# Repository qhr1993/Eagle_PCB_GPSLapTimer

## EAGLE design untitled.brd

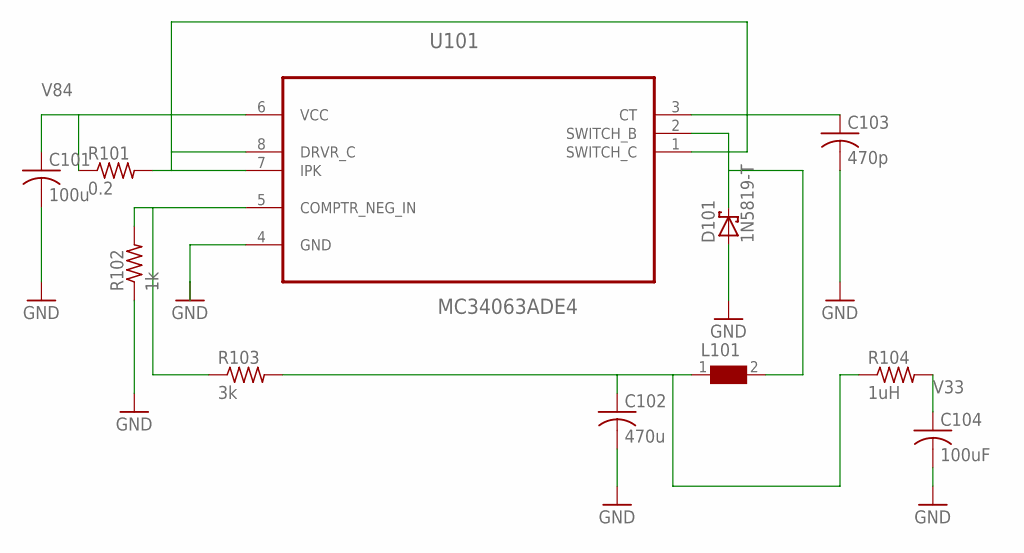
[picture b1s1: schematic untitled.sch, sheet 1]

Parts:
C101: 100u; C0805
C102: 470u; C0805
C103: 470p; C0805
C104: 100uF; C0805
D101: 1N5819-T; DO41-7.6
L101: WE-PD-7447714101_1030/1050; WE-PD_1030/1050
R101: 0.2; R0805
R102: 1k; R0805
R103: 3k; R0805
R104: 1uH; R0805
U101: MC34063ADE4; SOIC127P600X175-8N

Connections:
GND: C101.2, C102.2, C103.2, C104.2, D101.A, R102.1, U101.4 (GND); also elsewhere on the board
unnamed: C103.1, U101.3 (CT)
unnamed: R102.2, R103.1, U101.5 (COMPTR_NEG_IN)
unnamed: C102.1, L101.1, R103.2, R104.1
unnamed: R101.2, U101.1 (SWITCH_C), U101.7 (IPK), U101.8 (DRVR_C)
unnamed: D101.C, L101.2, U101.2 (SWITCH_B)
V33: C104.1, R104.2; also elsewhere on the board
V84: C101.1, R101.1, U101.6 (VCC); also elsewhere on the board

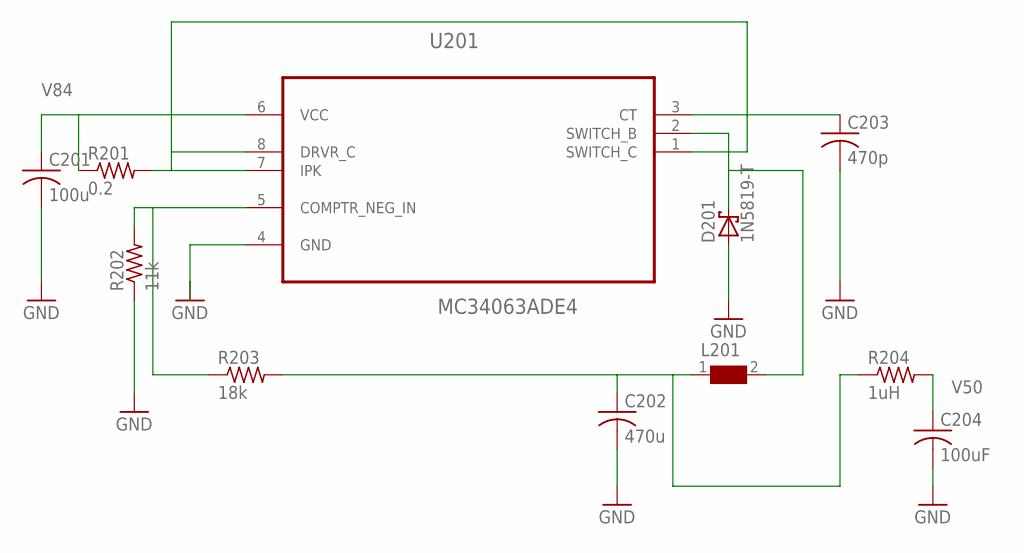
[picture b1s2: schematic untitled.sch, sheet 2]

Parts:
C201: 100u; C0805
C202: 470u; C0805
C203: 470p; C0805
C204: 100uF; C0805
D201: 1N5819-T; DO41-7.6
L201: WE-PD-7447714101_1030/1050; WE-PD_1030/1050
R201: 0.2; R0805
R202: 11k; R0805
R203: 18k; R0805
R204: 1uH; R0805
U201: MC34063ADE4; SOIC127P600X175-8N

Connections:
GND: C201.2, C202.2, C203.2, C204.2, D201.A, R202.1, U201.4 (GND); also elsewhere on the board
unnamed: C203.1, U201.3 (CT)
unnamed: R202.2, R203.1, U201.5 (COMPTR_NEG_IN)
unnamed: C202.1, L201.1, R203.2, R204.1
unnamed: R201.2, U201.1 (SWITCH_C), U201.7 (IPK), U201.8 (DRVR_C)
unnamed: D201.C, L201.2, U201.2 (SWITCH_B)
V50: C204.1, R204.2; also elsewhere on the board
V84: C201.1, R201.1, U201.6 (VCC); also elsewhere on the board

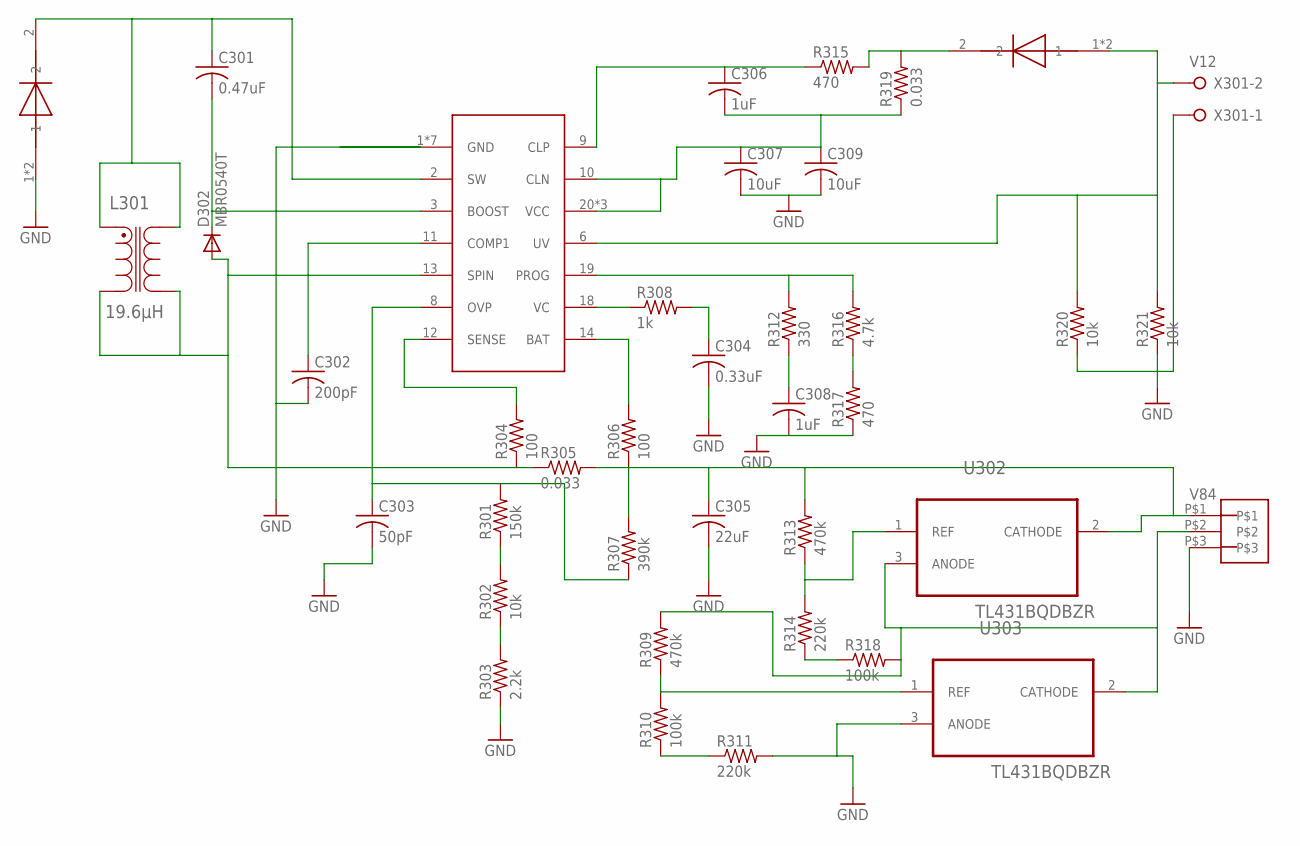
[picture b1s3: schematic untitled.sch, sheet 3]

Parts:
C301: 0.47uF; C0805
C302: 200pF; C0805
C303: 50pF; C0805
C304: 0.33uF; C0805
C305: 22uF; C0805
C306, C308: 1uF; C0805
C307, C309: 10uF; C0805
D301, D303: MBRD340; DPACK
D302: MBR0540T; SOD-123_MINI-SMA
J301: 3_PIN_JST-XH
L301: 19.6µH; INDM115115X635N
R301: 150k; R0805
R302, R320, R321: 10k; R0805
R303: 2.2k; R0805
R304, R306: 100; R0805
R305, R319: 0.033; R0805
R307: 390k; R0805
R308: 1k; R0805
R309, R313: 470k; R0805
R310, R318: 100k; R0805
R311, R314: 220k; R0805
R312: 330; R0805
R315, R317: 470; R0805
R316: 4.7k; R0805
U301: LT1511; SO24W
U302, U303: TL431BQDBZR; SOT95P237X112-3N
X301: W237-02P; W237-132

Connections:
GND: C302.2, C303.2, C304.2, C305.2, C307.2, C308.2, C309.2, D301.1, D301.3 (1), J301.P$3, R303.1, R311.2, R317.1, R320.1, R321.1, U301.1 (GND), U301.4 (GND), U301.5 (GND), U301.7 (GND), U301.16 (GND), U301.23 (GND), U301.24 (GND), U303.3 (ANODE), X301.1; also elsewhere on the board
unnamed: C301.1, D301.2, L301.1, L301.4, U301.2 (SW)
unnamed: D302.A, L301.2, L301.3, R304.1, R305.1, U301.13 (SPIN)
unnamed: C301.2, D302.C, U301.3 (BOOST)
unnamed: C302.1, U301.11 (COMP1)
unnamed: R304.2, U301.12 (SENSE)
unnamed: R306.2, U301.14 (BAT)
unnamed: R308.1, U301.18 (VC)
unnamed: C304.1, R308.2
unnamed: R312.2, R316.2, U301.19 (PROG)
unnamed: C308.1, R312.1
unnamed: C306.2, C307.1, C309.1, R319.1, U301.10 (CLN), U301.20 (VCC), U301.21 (VCC), U301.22 (VCC)
unnamed: C306.1, R315.1, U301.9 (CLP)
unnamed: D303.2, R315.2, R319.2
unnamed: R301.1, R302.2
unnamed: R302.1, R303.2
unnamed: R316.1, R317.2
unnamed: C303.1, R301.2, R307.1, U301.8 (OVP)
unnamed: R314.1, R318.1
unnamed: R313.1, R314.2, U302.1 (REF)
unnamed: R309.1, R310.2, U303.1 (REF)
unnamed: R310.1, R311.1
unnamed: J301.P$2, R309.2, R318.2, U302.3 (ANODE), U303.2 (CATHODE)
V12: D303.1, D303.3 (1), R320.2, R321.2, U301.6 (UV), X301.2
V84: C305.1, J301.P$1, R305.2, R306.1, R307.2, R313.2, U302.2 (CATHODE); also elsewhere on the board

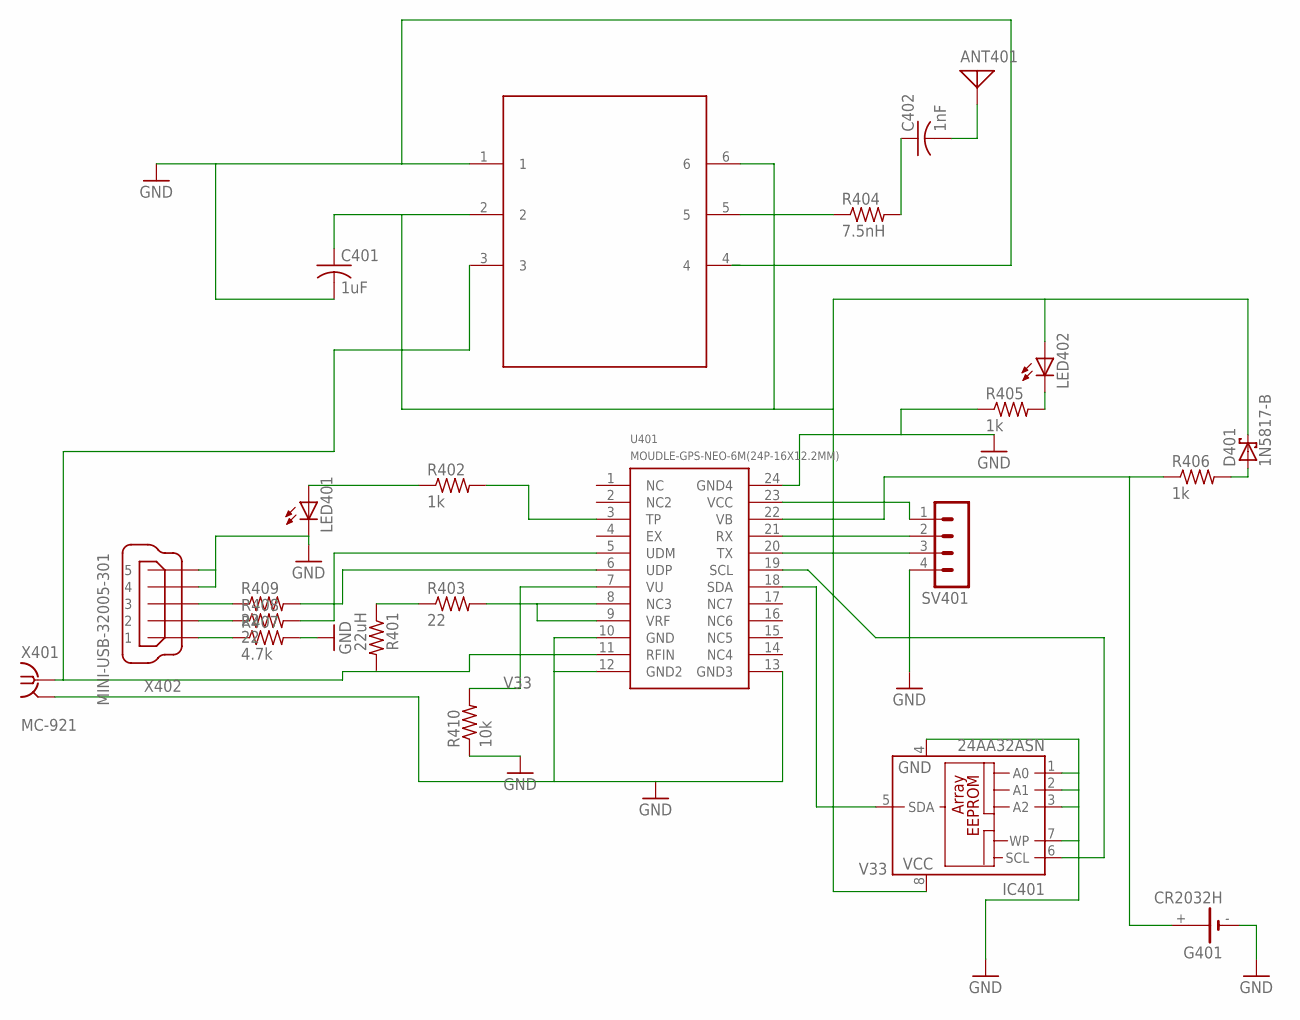
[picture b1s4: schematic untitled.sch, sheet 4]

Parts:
ANT401: ANTENNA; PAD-01
C401: 1uF; C0603
C402: 1nF; C0603
D401: 1N5817-B; DO41-7.6
G401: CR2032H
IC401: 24AA32ASN; SO-08
LED401, LED402: LEDCHIP-LED0805; CHIP-LED0805
R401: 22uH; R0603
R402, R405, R406: 1k; R0805
R403, R408, R409: 22; R0603
R404: 7.5nH; R0603
R407: 4.7k; R0603
R410: 10k; R0603
SV401: MA04-1
U401: MOUDLE-GPS-NEO-6M(24P-16X12.2MM); GPS24P-SMD-1.1-16X12.2MM
U402: INF-TSLP-6-2_V_1; INF-TSLP-6-2_V_1PRIMARY
X401: MC-921
X402: MINI-USB-32005-301; 32005-301

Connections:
GND: C401.2, G401.-, IC401.1 (A0), IC401.2 (A1), IC401.3 (A2), IC401.4 (GND), IC401.7 (WP), LED401.C, R405.1, R407.2, R410.1, SV401.4, U401.10 (GND), U401.12 (GND2), U401.13 (GND3), U401.24 (GND4), U402.1, X401.2@1 (GND), X401.2@2 (GND), X402.4, X402.5; also elsewhere on the board
unnamed: LED401.A, R402.1
unnamed: SV401.3, U401.20 (TX)
unnamed: SV401.2, U401.21 (RX)
unnamed: IC401.6 (SCL), U401.19 (SCL)
unnamed: IC401.5 (SDA), U401.18 (SDA)
unnamed: R402.2, U401.3 (TP)
unnamed: R403.2, U401.8 (NC3), U401.9 (VRF)
unnamed: G401.+, R406.1, U401.22 (VB)
unnamed: D401.A, R406.2
unnamed: LED402.C, R405.2
unnamed: R401.1, R403.1
unnamed: R408.2, U401.5 (UDM)
unnamed: R409.2, U401.6 (UDP)
unnamed: ANT401.1, C402.2
unnamed: R401.2, U401.11 (RFIN), U402.3, X401.1
unnamed: R404.1, U402.5
unnamed: C402.1, R404.2
unnamed: R407.1, X402.1
unnamed: R409.1, X402.3
unnamed: R408.1, X402.2
V33: C401.1, D401.C, IC401.8 (VCC), LED402.A, R410.2, SV401.1, U401.7 (VU), U401.23 (VCC), U402.2, U402.6; also elsewhere on the board

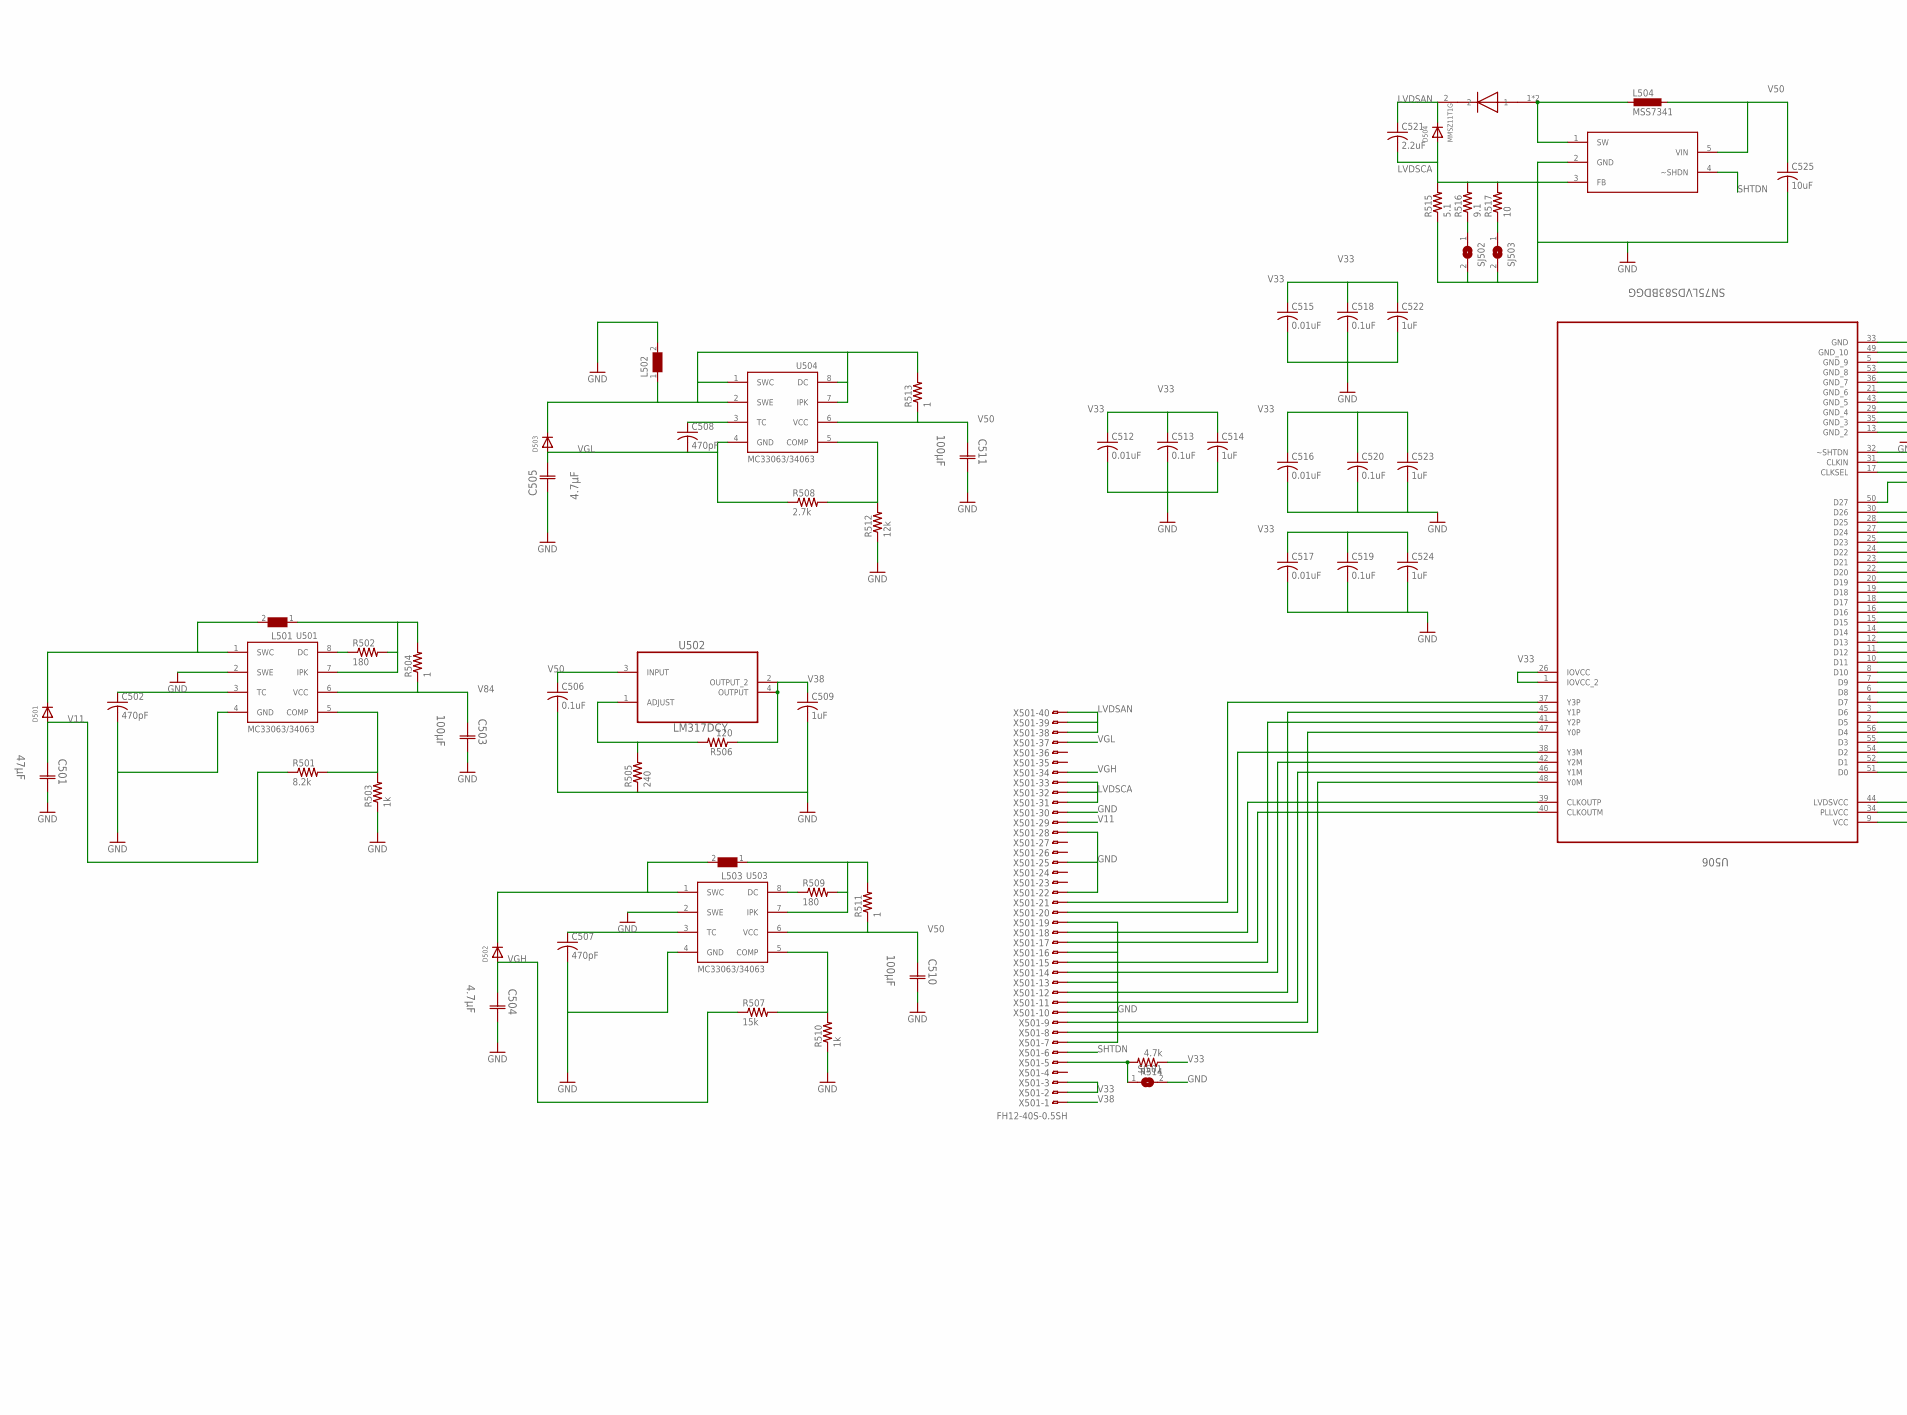
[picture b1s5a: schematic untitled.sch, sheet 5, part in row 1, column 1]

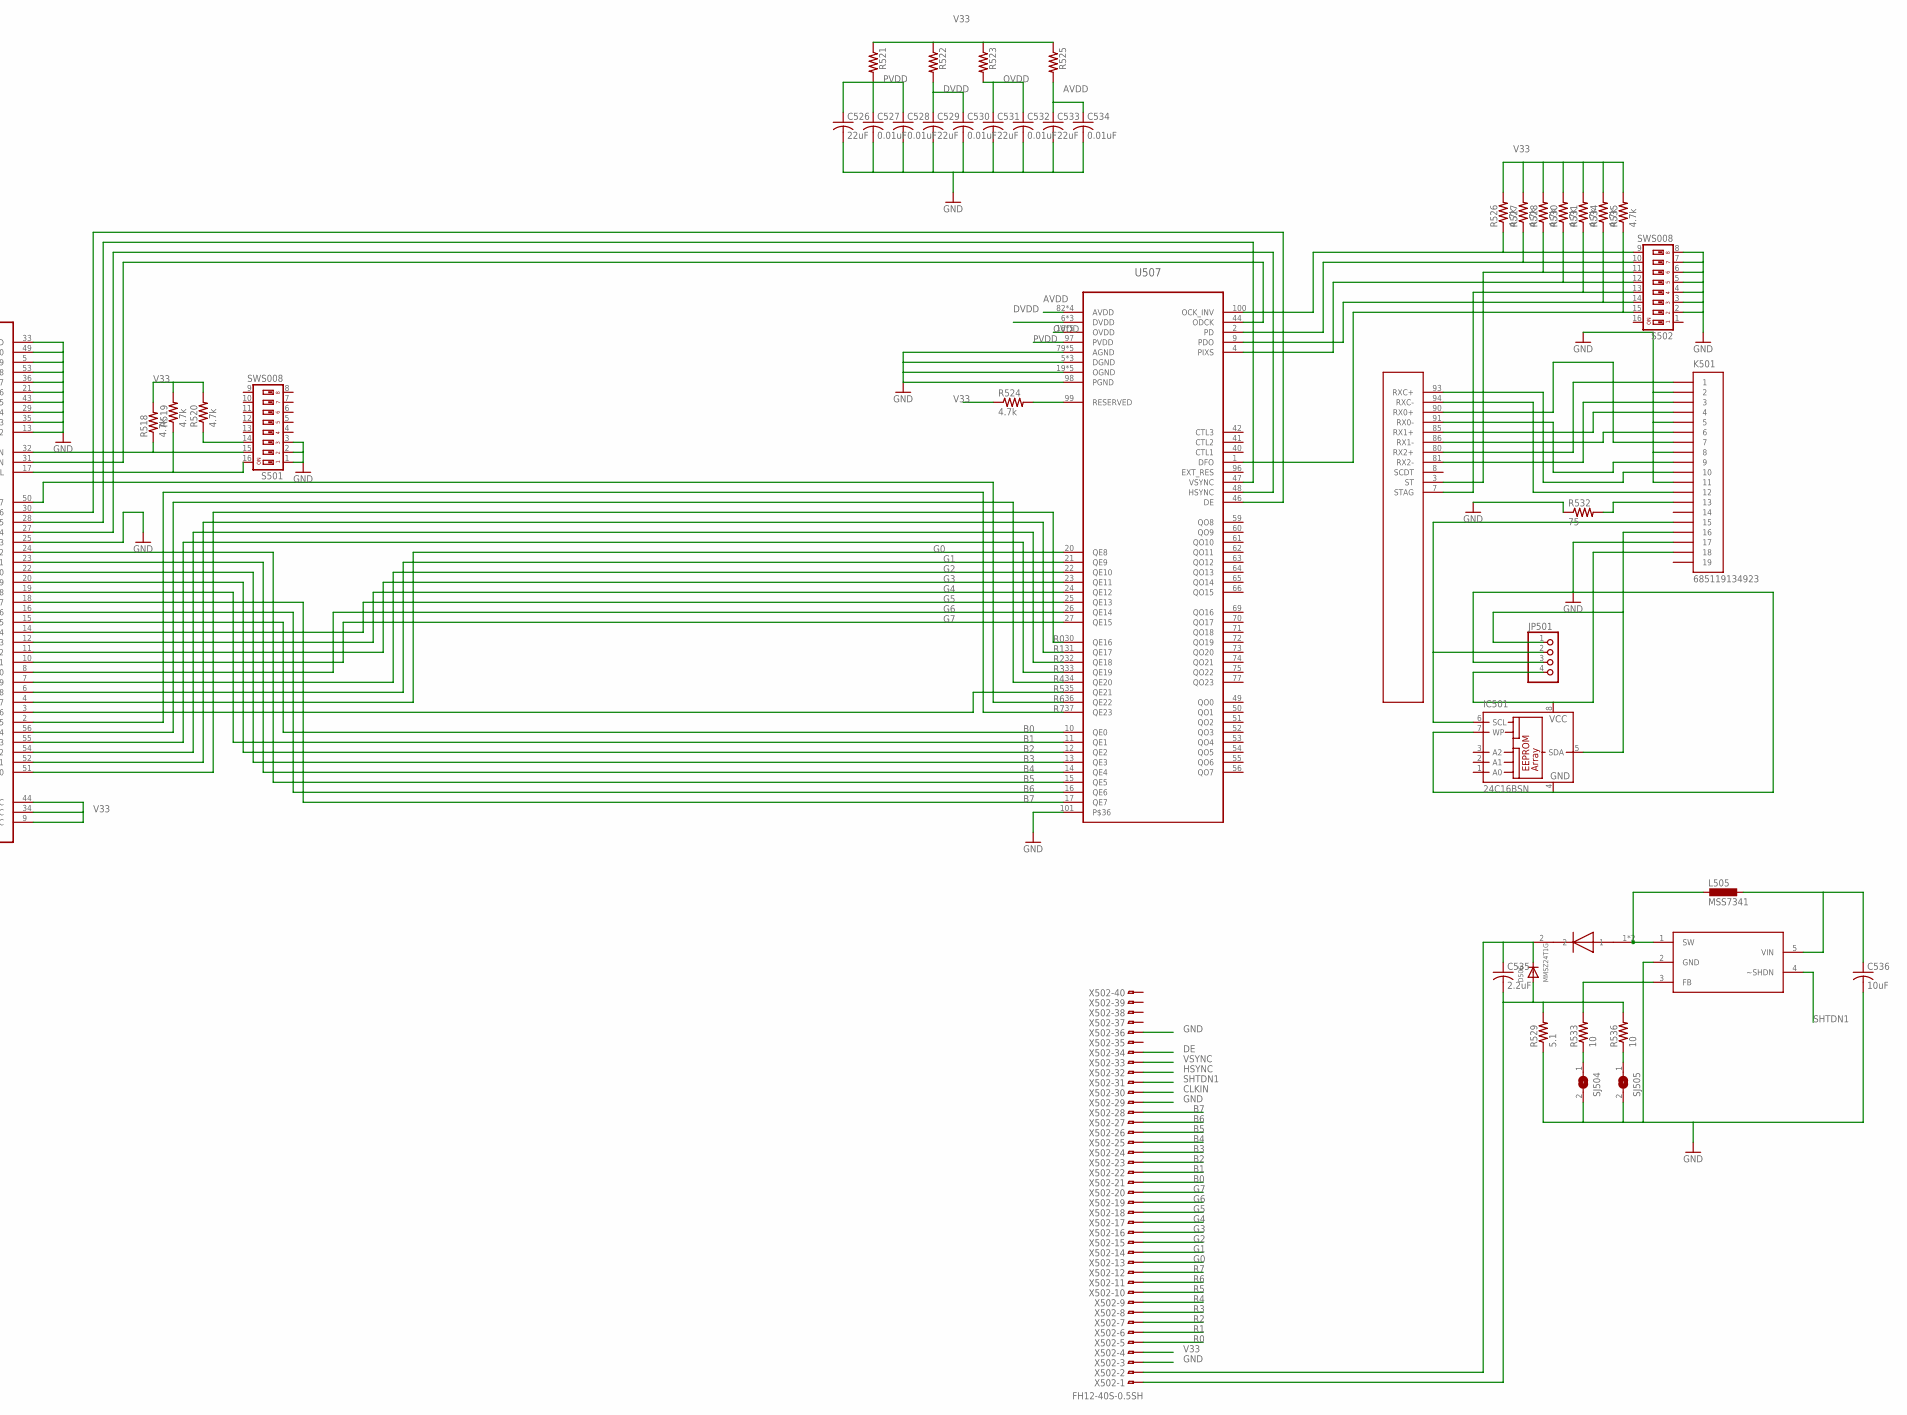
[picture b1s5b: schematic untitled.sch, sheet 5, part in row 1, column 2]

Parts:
C501: 47µF; CAPCP6032X280N
C502, C507, C508: 470pF; C0603
C503, C510, C511: 100µF; CAPCP6032X280N
C504, C505: 4.7µF; CAPCP6032X280N
C506, C513, C518, C519, C520: 0.1uF; C0603
C509, C514, C522, C523, C524: 1uF; C0603
C512, C515, C516, C517, C527, C528, C530, C532, C534: 0.01uF; C0603
C521, C535: 2.2uF; C0805
C525, C536: 10uF; C0805
C526, C529, C531, C533: 22uF; C0603
D501, D502, D503: DIODESOD-123; SOD-123
D504: MMSZ11T1G; SOD-123
D505, D507: MBRD340; DPACK
D506: MMSZ24T1G; SOD-123
IC501: 24C16BSN; SO-08
JP501: PINHD-1X4; 1X04
K501: 685119134923
L501, L502, L503: WE-PD-7447714101_1030/1050; WE-PD_1030/1050
L504, L505: MSS7341
R501: 8.2k; R0603
R502, R509: 180; R0603
R503, R510: 1k; R0603
R504, R511, R513: 1; R0603
R505: 240; R0603
R506: 120; R0603
R507: 15k; R0603
R508: 2.7k; R0603
R512: 12k; R0603
R514, R518, R519, R520, R524, R526, R527, R528, R530, R531, R534, R535: 4.7k; R0603
R515, R529: 5.1; R0603
R516: 9.1; R0603
R517, R533, R536: 10; R0603
R521, R522, R523, R525: R-US_R0805; R0805
R532: 75; R0603
S501, S502: SWS008; SMS-008
SJ501, SJ502, SJ503, SJ504, SJ505: SJ
U501, U503, U504: MC33063/MC34063D; SO08
U502: LM317DCY; SOT230P700X180-4N
U505, U508: FAN5333BSX; SOT23-5L
U506: SN75LVDS83BDGG; SOP50P810X120-56N
U507: TPF401; QFP50P1600X1600X120-101N
X501, X502: FH12-40S-0.5SH

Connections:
AVDD: C533.1, C534.1, R525.2, U507.82 (AVDD), U507.84 (AVDD), U507.88 (AVDD), U507.95 (AVDD)
B0: U506.15 (D15), U507.10 (QE0), X502.21
B1: U506.19 (D18), U507.11 (QE1), X502.22
B2: U506.20 (D19), U507.12 (QE2), X502.23
B3: U506.22 (D20), U507.13 (QE3), X502.24
B4: U506.23 (D21), U507.14 (QE4), X502.25
B5: U506.24 (D22), U507.15 (QE5), X502.26
B6: U506.16 (D16), U507.16 (QE6), X502.27
B7: U506.18 (D17), U507.17 (QE7), X502.28
CLKIN: U506.31 (CLKIN), U507.44 (ODCK), X502.30
DE: U506.30 (D26), U507.46 (DE), X502.34
DVDD: C529.1, C530.1, R522.2, U507.6 (DVDD), U507.38 (DVDD), U507.67 (DVDD)
G0: U506.4 (D7), U507.20 (QE8), X502.13
G1: U506.6 (D8), U507.21 (QE9), X502.14
G2: U506.7 (D9), U507.22 (QE10), X502.15
G3: U506.11 (D12), U507.23 (QE11), X502.16
G4: U506.12 (D13), U507.24 (QE12), X502.17
G5: U506.14 (D14), U507.25 (QE13), X502.18
G6: U506.8 (D10), U507.26 (QE14), X502.19
G7: U506.10 (D11), U507.27 (QE15), X502.20
GND: C501.2 (C2), C502.2, C503.2 (C2), C504.2 (C2), C505.1 (C1), C506.2, C507.2, C509.2, C510.2 (C2), C511.2 (C2), C512.2, C513.2, C514.2, C515.2, C516.2, C517.2, C518.2, C519.2, C520.2, C522.2, C523.2, C524.2, C525.2, C526.2, C527.2, C528.2, C529.2, C530.2, C531.2, C532.2, C533.2, C534.2, C536.2, IC501.4 (GND), IC501.7 (WP), JP501.3, K501.2, K501.5, K501.8, K501.11, K501.17, L502.2, R503.1, R505.1, R510.1, R512.1, R515.1, R529.1, R532.1, S501.1, S501.2, S501.3, S502.2, S502.3, S502.4, S502.5, S502.6, S502.7, S502.8, SJ501.2, SJ502.2, SJ503.2, SJ504.2, SJ505.2, U501.2 (SWE), U501.4 (GND), U503.2 (SWE), U503.4 (GND), U505.2 (GND), U506.5 (GND_9), U506.13 (GND_2), U506.21 (GND_6), U506.25 (D23), U506.29 (GND_4), U506.33 (GND), U506.35 (GND_3), U506.36 (GND_7), U506.43 (GND_5), U506.49 (GND_10), U506.53 (GND_8), U507.5 (DGND), U507.19 (OGND), U507.28 (OGND), U507.39 (DGND), U507.45 (OGND), U507.58 (OGND), U507.68 (DGND), U507.76 (OGND), U507.79 (AGND), U507.83 (AGND), U507.87 (AGND), U507.89 (AGND), U507.92 (AGND), U507.98 (PGND), U507.101, U508.2 (GND), X501.7, X501.10, X501.13, X501.16, X501.19, X501.22, X501.25, X501.28, X501.30, X502.3, X502.29, X502.36; also elsewhere on the board
HSYNC: U506.27 (D24), U507.48 (HSYNC), X502.32
LVDSAN: C521.1, D504.C, D505.2, X501.38, X501.39, X501.40
LVDSCA: C521.2, D504.A, R515.2, R516.2, R517.2, U505.3 (FB), X501.31, X501.32, X501.33
unnamed: R524.2, U507.99 (RESERVED)
unnamed: R526.1, S502.9, U507.100 (OCK_INV)
unnamed: R527.1, S502.10, U507.2 (PD)
unnamed: R528.1, S502.11, U507.3 (ST)
unnamed: R530.1, S502.12, U507.4 (PIXS)
unnamed: R531.1, S502.13, U507.7 (STAG)
unnamed: R534.1, S502.14, U507.9 (PDO)
unnamed: R535.1, S502.15, U507.1 (DFO)
unnamed: K501.1, U507.80 (RX2+)
unnamed: K501.3, U507.81 (RX2-)
unnamed: K501.4, U507.85 (RX1+)
unnamed: K501.6, U507.86 (RX1-)
unnamed: K501.7, U507.90 (RX0+)
unnamed: K501.9, U507.91 (RX0-)
unnamed: K501.10, U507.93 (RXC+)
unnamed: K501.12, U507.94 (RXC-)
unnamed: IC501.8 (VCC), JP501.4, K501.18
unnamed: IC501.6 (SCL), JP501.2, K501.15
unnamed: IC501.5 (SDA), JP501.1, K501.16
unnamed: K501.13, R532.2
unnamed: D505.1, D505.3 (1), L504.1, U505.1 (SW)
unnamed: R516.1, SJ502.1
unnamed: R517.1, SJ503.1
unnamed: D507.1, D507.3 (1), L505.1, U508.1 (SW)
unnamed: C535.1, D506.C, D507.2, X502.2
unnamed: C535.2, D506.A, R529.2, R533.2, R536.2, U508.3 (FB), X502.1
unnamed: R536.1, SJ505.1
unnamed: R533.1, SJ504.1
unnamed: C508.1, U504.3 (TC)
unnamed: D503.C, L502.1, R513.2, U504.1 (SWC), U504.2 (SWE), U504.7 (IPK), U504.8 (DC)
unnamed: R508.2, R512.2, U504.5 (COMP)
unnamed: U506.37 (Y3P), X501.21
unnamed: U506.38 (Y3M), X501.20
unnamed: U506.39 (CLKOUTP), X501.18
unnamed: U506.40 (CLKOUTM), X501.17
unnamed: U506.41 (Y2P), X501.15
unnamed: U506.42 (Y2M), X501.14
unnamed: U506.45 (Y1P), X501.12
unnamed: U506.46 (Y1M), X501.11
unnamed: U506.47 (Y0P), X501.9
unnamed: U506.48 (Y0M), X501.8
unnamed: R505.2, R506.2, U502.1 (ADJUST)
unnamed: R514.2, SJ501.1, X501.5
unnamed: R519.1, S501.16, U506.17 (CLKSEL)
unnamed: C507.1, U503.3 (TC)
unnamed: D502.C, L503.2, U503.1 (SWC)
unnamed: R507.2, R510.2, U503.5 (COMP)
unnamed: L503.1, R509.2, R511.2, U503.7 (IPK)
unnamed: R509.1, U503.8 (DC)
unnamed: C502.1, U501.3 (TC)
unnamed: D501.C, L501.2, U501.1 (SWC)
unnamed: R501.2, R503.2, U501.5 (COMP)
unnamed: L501.1, R502.2, R504.2, U501.7 (IPK)
unnamed: R502.1, U501.8 (DC)
OVDD: C531.1, C532.1, R523.2, U507.18 (OVDD), U507.29 (OVDD), U507.43 (OVDD), U507.57 (OVDD), U507.78 (OVDD)
PVDD: C526.1, C527.1, C528.1, R521.2, U507.97 (PVDD)
R0: U506.51 (D0), U507.30 (QE16), X502.5
R1: U506.52 (D1), U507.31 (QE17), X502.6
R2: U506.54 (D2), U507.32 (QE18), X502.7
R3: U506.55 (D3), U507.33 (QE19), X502.8
R4: U506.56 (D4), U507.34 (QE20), X502.9
R5: U506.3 (D6), U507.35 (QE21), X502.10
R6: U506.50 (D27), U507.36 (QE22), X502.11
R7: U506.2 (D5), U507.37 (QE23), X502.12
SHTDN: R518.1, S501.15, U505.4 (~SHDN), U506.32 (~SHTDN), X501.6
SHTDN1: R520.1, S501.14, U508.4 (~SHDN), X502.31
V11: C501.1 (C1), D501.A, R501.1, X501.29
V33: C512.1, C513.1, C514.1, C515.1, C516.1, C517.1, C518.1, C519.1, C520.1, C522.1, C523.1, C524.1, R514.1, R518.2, R519.2, R520.2, R521.1, R522.1, R523.1, R524.1, R525.1, R526.2, R527.2, R528.2, R530.2, R531.2, R534.2, R535.2, U506.1 (IOVCC_2), U506.9 (VCC), U506.26 (IOVCC), U506.34 (PLLVCC), U506.44 (LVDSVCC), X501.2, X501.3, X502.4; also elsewhere on the board
V38: C509.1, R506.1, U502.2 (OUTPUT_2), U502.4 (OUTPUT), X501.1
V50: C506.1, C510.1 (C1), C511.1 (C1), C525.1, C536.1, L504.2, L505.2, R511.1, R513.1, U502.3 (INPUT), U503.6 (VCC), U504.6 (VCC), U505.5 (VIN), U508.5 (VIN); also elsewhere on the board
V84: C503.1 (C1), R504.1, U501.6 (VCC); also elsewhere on the board
VGH: C504.1 (C1), D502.A, R507.1, X501.34
VGL: C505.2 (C2), C508.2, D503.A, R508.1, U504.4 (GND), X501.37
VSYNC: U506.28 (D25), U507.47 (VSYNC), X502.33

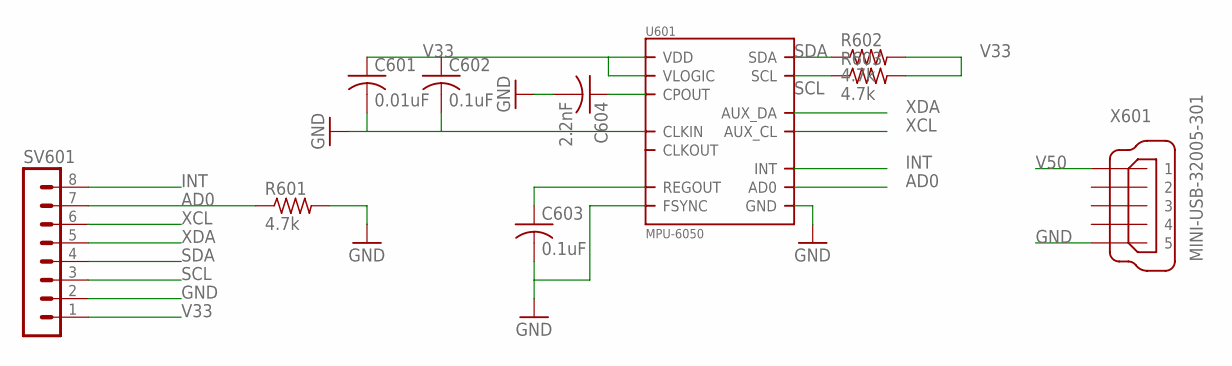
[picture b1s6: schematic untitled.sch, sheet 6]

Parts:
C601: 0.01uF; C0603
C602, C603: 0.1uF; C0603
C604: 2.2nF; C0603
R601, R602, R603: 4.7k; R0603
SV601: MA08-1
U601: MPU-6050; QFN.24.4X4
X601: MINI-USB-32005-301; 32005-301

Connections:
AD0: R601.1, SV601.7, U601.9 (AD0)
GND: C601.2, C602.2, C603.2, C604.2, R601.2, SV601.2, U601.1 (CLKIN), U601.11 (FSYNC), U601.18 (GND), X601.5; also elsewhere on the board
INT: SV601.8, U601.12 (INT)
unnamed: C604.1, U601.20 (CPOUT)
unnamed: C603.1, U601.10 (REGOUT)
SCL: R603.1, SV601.3, U601.23 (SCL)
SDA: R602.1, SV601.4, U601.24 (SDA)
V33: C601.1, C602.1, R602.2, R603.2, SV601.1, U601.8 (VLOGIC), U601.13 (VDD); also elsewhere on the board
V50: X601.1; also elsewhere on the board
XCL: SV601.6, U601.7 (AUX_CL)
XDA: SV601.5, U601.6 (AUX_DA)

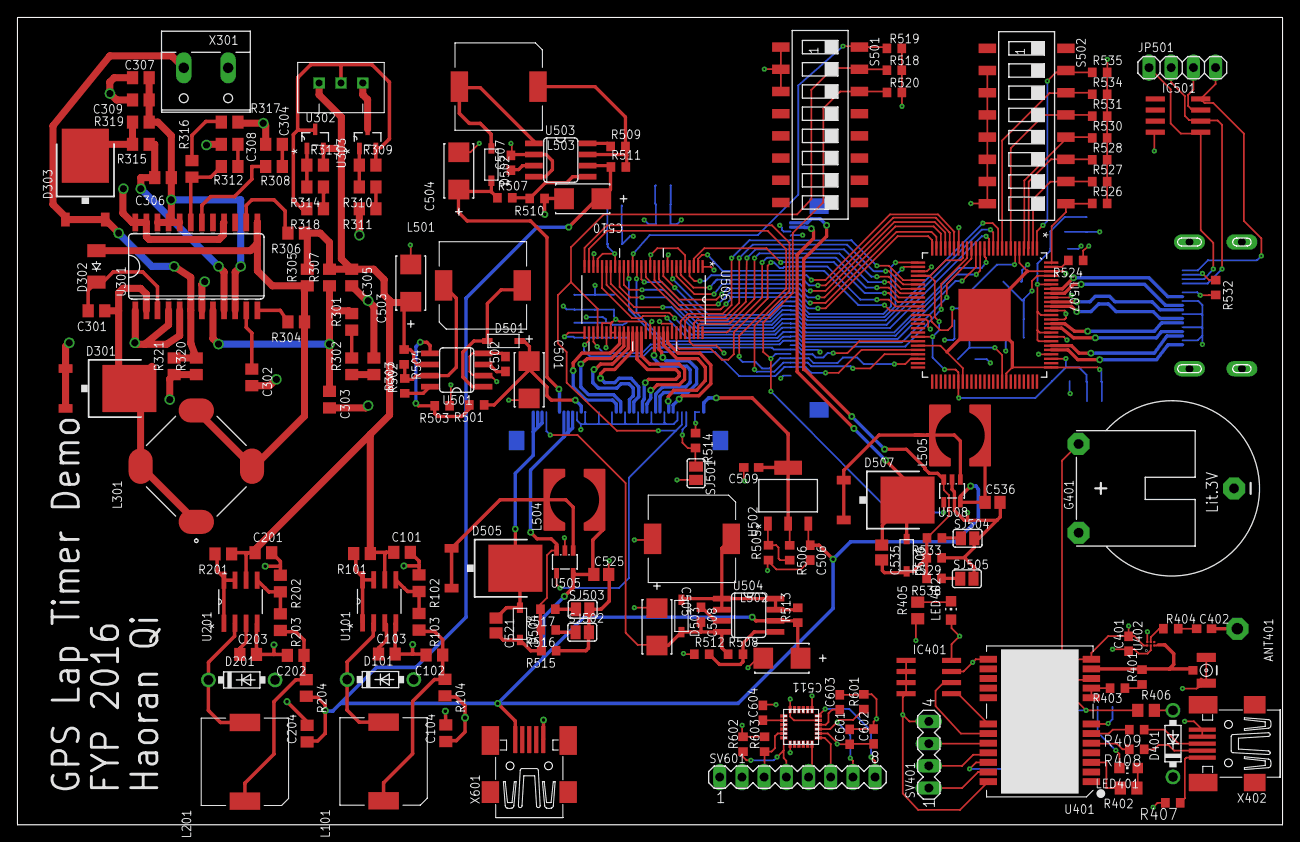
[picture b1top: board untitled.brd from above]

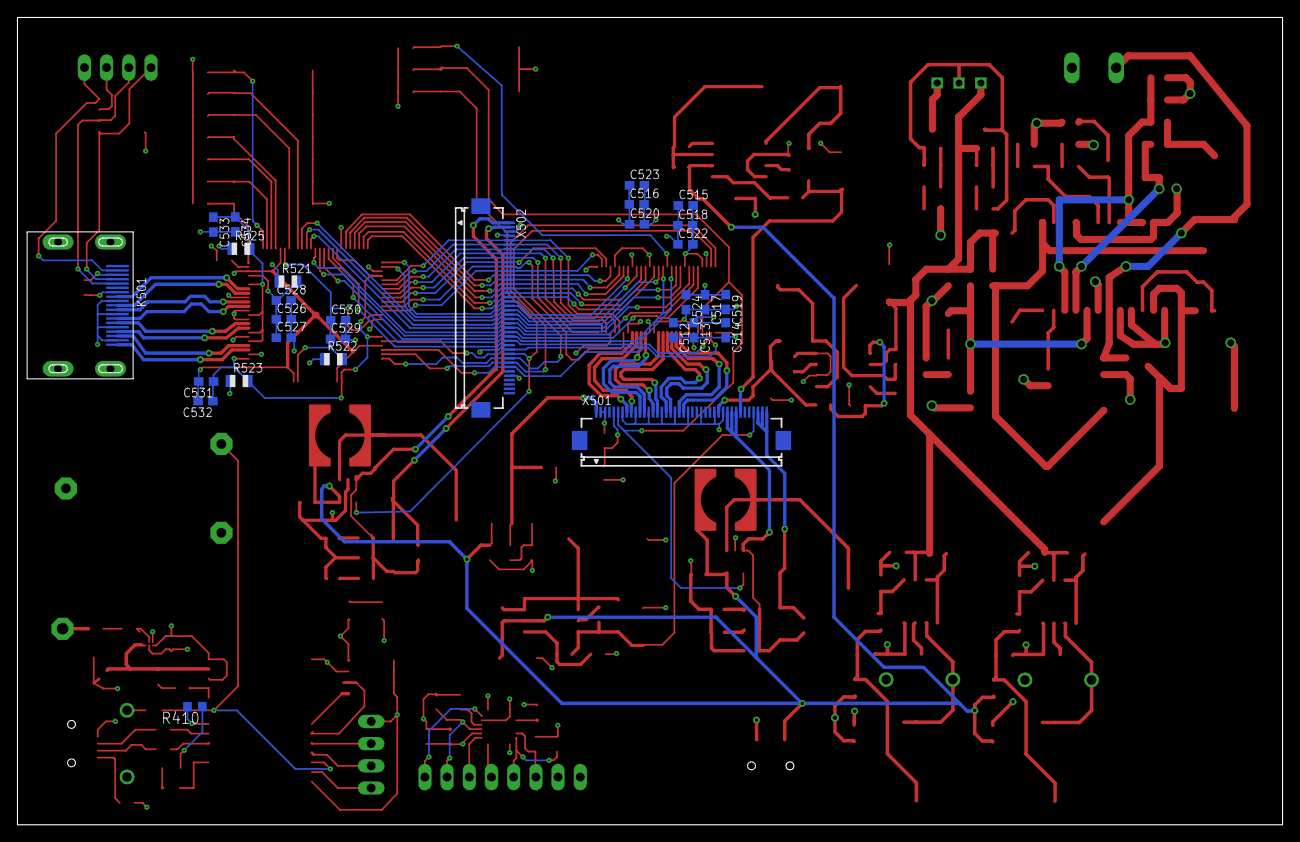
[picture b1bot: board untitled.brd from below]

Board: 4 copper layers, 144.8 x 92.4 mm, 198 parts (29 on the bottom side), 159 nets.

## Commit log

2016-04-21 Added files via upload

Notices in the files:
parts and their libraries:
Eagle_INPUT_OUTPUT_CONNECTORS_rev15d: Copyright: Würth Elektronik
